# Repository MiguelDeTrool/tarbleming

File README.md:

# tarbleming
Arduino Nano based random looping sequencer Eurorack module

This is my take on the Music Thing Modular Turing Machine/Mutable Instruments Marbles, in an easier to implement fashion, with easily available through-hole parts. I must warn anyone attempting this that I have not tested these exact PCBs, only an earlier prototype, that I then made minor modifications to for this version. I am quite confident that they will work, and feel free to send me a message if you decide to try this out. I wouldn't recommend this to a complete beginner, as I have provided no build guide.

You'll also notice a manual is missing. Basic functionality to get up and running is send it a clock signal. Each sequence, wether Gate or CV, can have it's own length. Tap the corresponding button for however many steps you want, then do a quick double tap to confirm that value. Turn a sequence's Randomness knob fully clockwise for it to constantly change, and fully counter-clockwise for it to lock in a looping pattern. And again, if you have questions, feel free to send a message.

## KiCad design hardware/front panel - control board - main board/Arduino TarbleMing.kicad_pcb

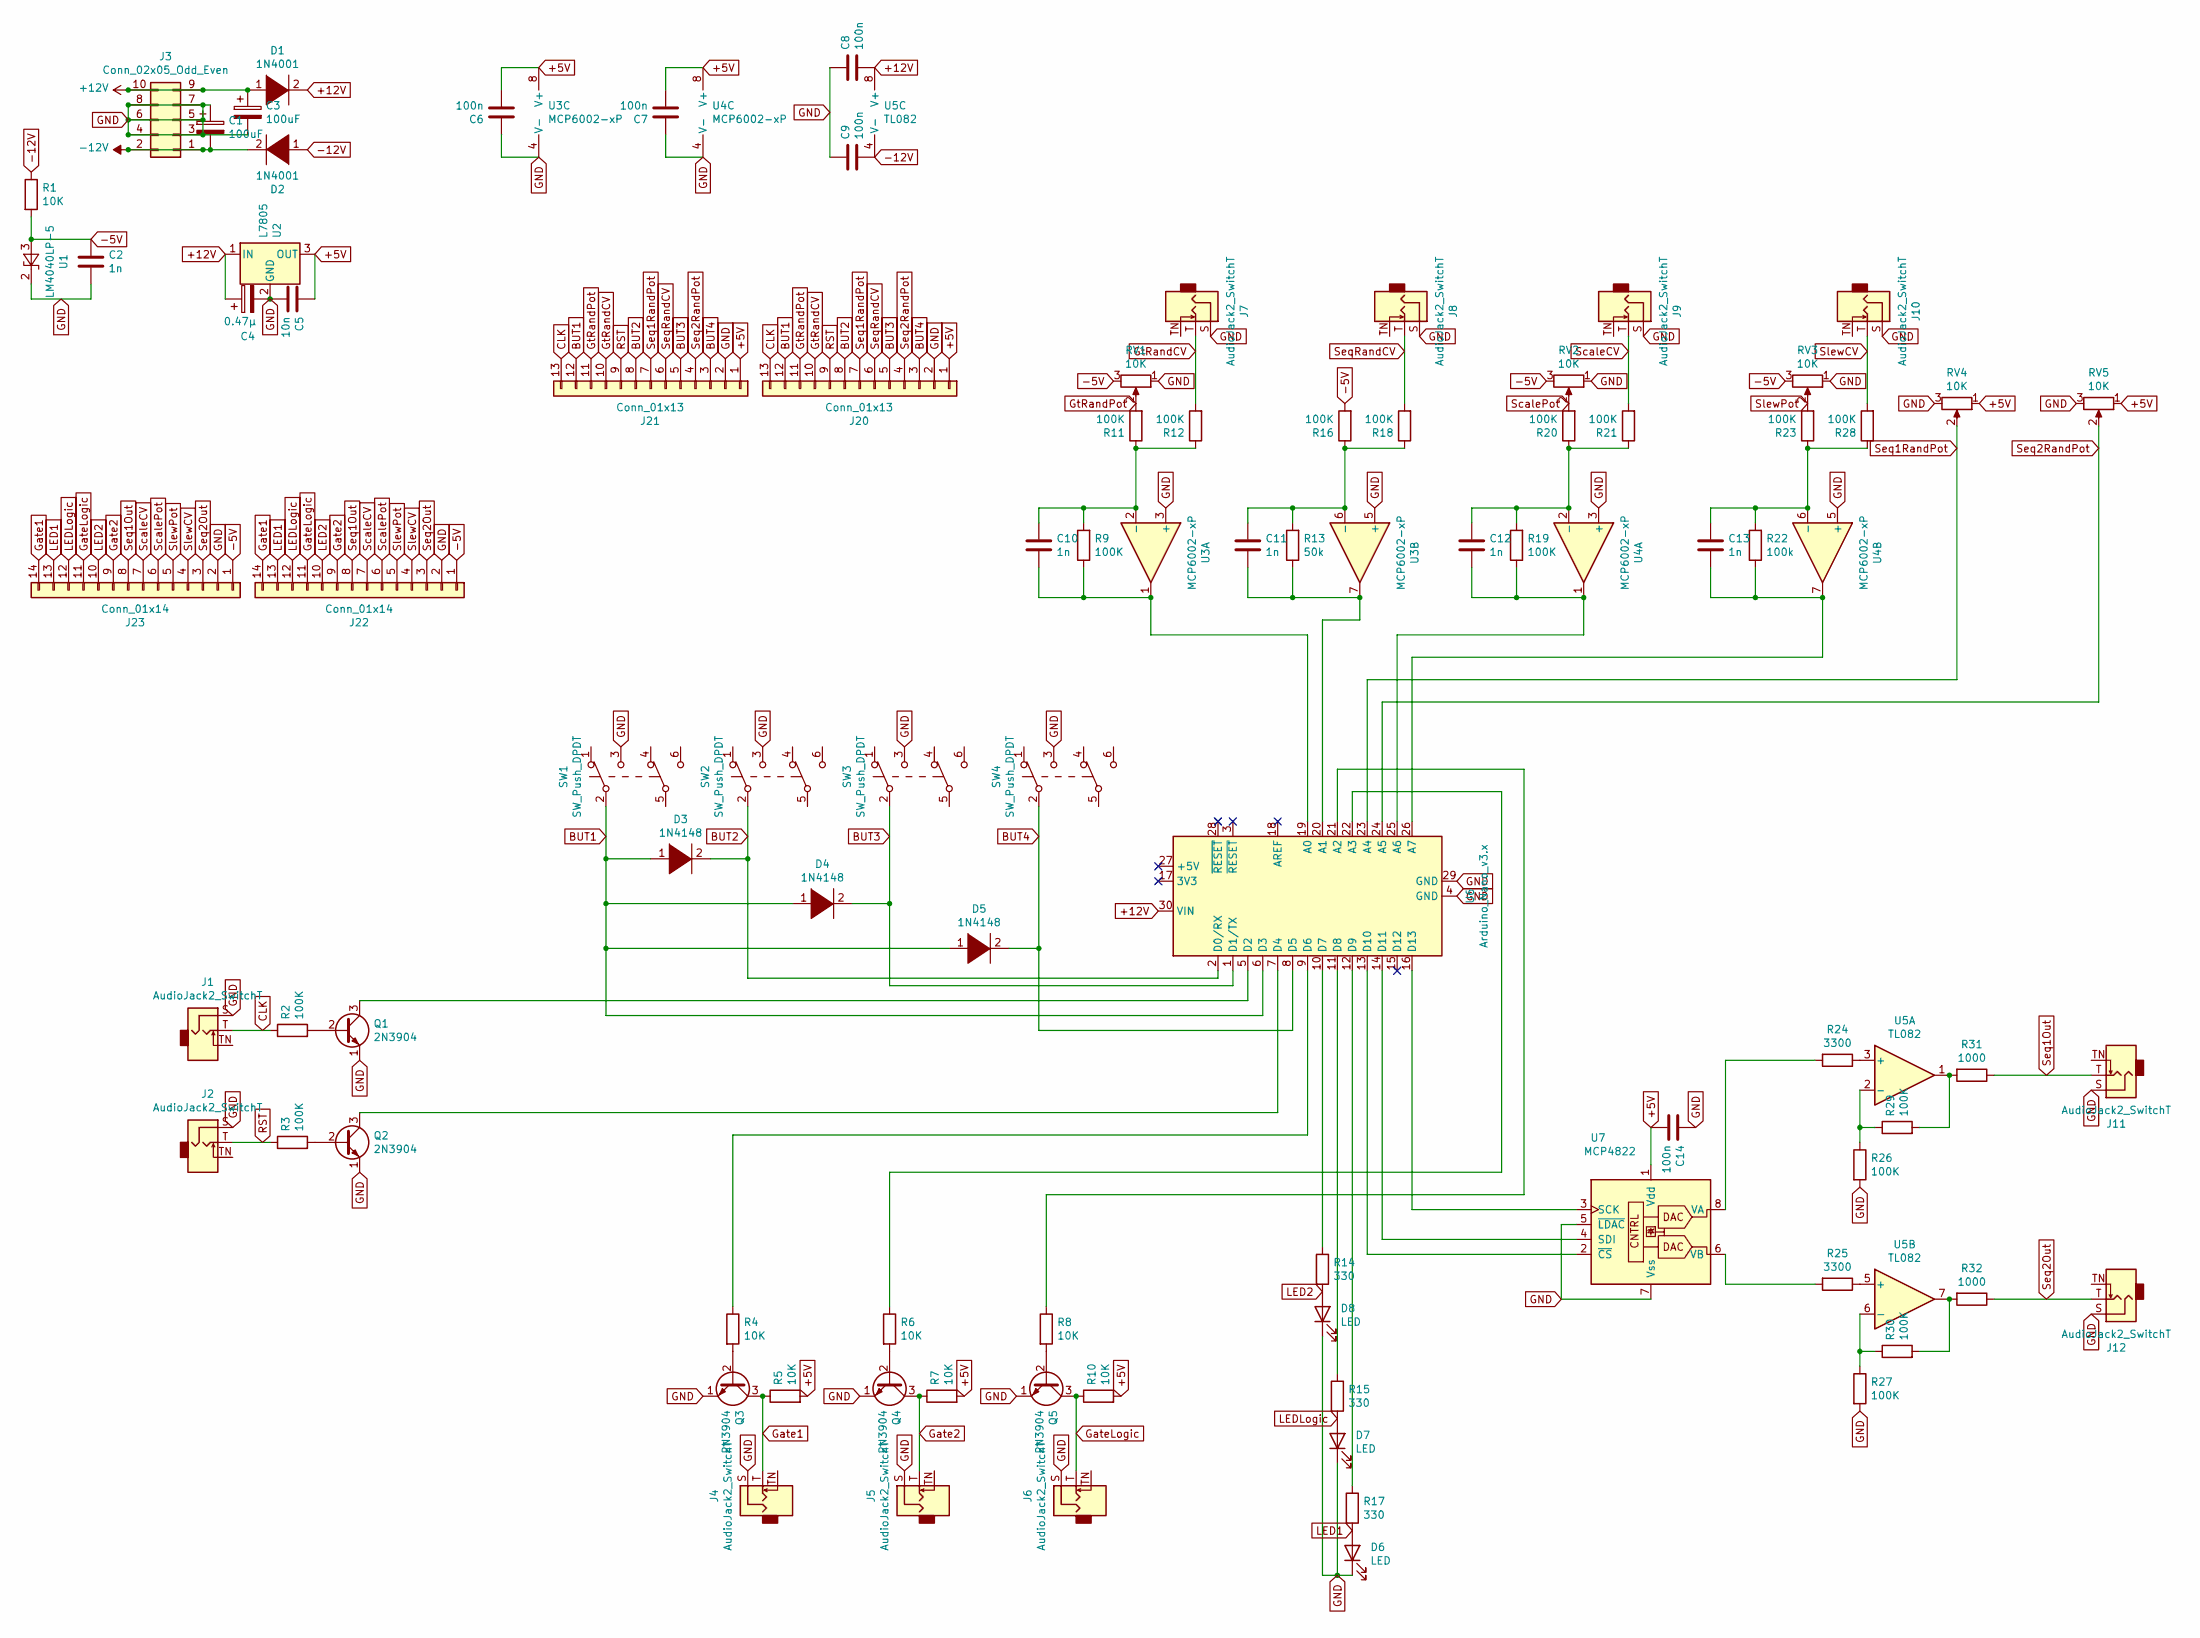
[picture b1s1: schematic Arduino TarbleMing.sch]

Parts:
C1, C3: 100uF; CP_Radial_D6.3mm_P2.50mm
C2, C10, C11, C12, C13: 1n; C_Disc_D3.8mm_W2.6mm_P2.50mm
C4: 0.47µ; C_Disc_D3.8mm_W2.6mm_P2.50mm
C5: 10n; C_Disc_D3.8mm_W2.6mm_P2.50mm
C6, C7, C8, C9, C14: 100n; C_Disc_D3.8mm_W2.6mm_P2.50mm
D1, D2: 1N4001; D_DO-15_P10.16mm_Horizontal
D3, D4, D5: 1N4148; D_DO-35_SOD27_P7.62mm_Horizontal
D6, D7, D8: LED; LED_D3.0mm
J1, J2, J4, J5, J6, J7, J8, J9, J10, J11, J12: AudioJack2_SwitchT; ModdedThonkiconn
J3: Conn_02x05_Odd_Even; PinHeader_2x05_P2.54mm_Vertical
J20, J21: Conn_01x13; PinHeader_1x13_P2.54mm_Vertical
J22, J23: Conn_01x14; PinHeader_1x14_P2.54mm_Vertical
Q1, Q2, Q3, Q4, Q5: 2N3904; TO-92_Inline
R1, R4, R5, R6, R7, R8, R10: 10K; R_Axial_DIN0207_L6.3mm_D2.5mm_P7.62mm_Horizontal
R2, R3, R9, R11, R12, R16, R18, R19, R20, R21, R23, R26, R27, R28, R29, R30: 100K; R_Axial_DIN0207_L6.3mm_D2.5mm_P7.62mm_Horizontal
R13: 50k; R_Axial_DIN0207_L6.3mm_D2.5mm_P7.62mm_Horizontal
R14, R15, R17: 330; R_Axial_DIN0207_L6.3mm_D2.5mm_P7.62mm_Horizontal
R22: 100k; R_Axial_DIN0207_L6.3mm_D2.5mm_P7.62mm_Horizontal
R24, R25: 3300; R_Axial_DIN0207_L6.3mm_D2.5mm_P7.62mm_Horizontal
R31, R32: 1000; R_Axial_DIN0207_L6.3mm_D2.5mm_P7.62mm_Horizontal
RV1, RV2, RV3, RV4, RV5: 10K; ModdedPotentiometer
SW1, SW2, SW3, SW4: SW_Push_DPDT; DPDT_Momentary_Push_Button_Switch
U1: LM4040LP-5; TO-92_Inline
U2: L7805; TO-220-3_Horizontal_TabDown
U3, U4: MCP6002-xP; DIP-8_W7.62mm_Socket_LongPads
U5: TL082; DIP-8_W7.62mm_Socket_LongPads
U6: Arduino_Nano_v3.x; Arduino_Nano
U7: MCP4822; DIP-8_W7.62mm_Socket_LongPads

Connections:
+5V: C5.1, C6.2, C7.2, C14.2, J20.1, J21.1, R5.2, R7.2, R10.2, RV4.1, RV5.1, U2.3 (OUT), U3.8 (V+), U4.8 (V+), U7.1 (Vdd)
+12V: C3.1, C4.1, C8.2, D1.1 (K), D1.2 (A), J3.9, J3.10, U2.1 (IN), U5.8 (V+), U6.30 (VIN)
-5V: C2.1, J22.1, J23.1, R1.2, R16.2, RV1.3, RV2.3, RV3.3, U1.3 (A)
-12V: C1.2, C9.2, D2.1 (K), D2.2 (A), J3.1, J3.2, R1.1, U5.4 (V-)
BUT1: D3.1 (K), D4.1 (K), D5.1 (K), J20.12, J21.12, SW1.2 (B), U6.6 (D3)
BUT2: D3.2 (A), J20.8, J21.8, SW2.2 (B), U6.2 (D0/RX)
BUT3: D4.2 (A), J20.5, J21.5, SW3.2 (B), U6.1 (D1/TX)
BUT4: D5.2 (A), J20.3, J21.3, SW4.2 (B), U6.8 (D5)
CLK: J1.T, J20.13, J21.13, R2.1
GND: C1.1, C2.2, C3.2, C4.2, C5.2, C6.1, C7.1, C8.1, C9.1, C14.1, D6.1 (K), D7.1 (K), D8.1 (K), J1.S, J2.S, J3.3, J3.4, J3.5, J3.6, J3.7, J3.8, J4.S, J5.S, J6.S, J7.S, J8.S, J9.S, J10.S, J11.S, J12.S, J20.2, J21.2, J22.2, J23.2, Q1.1 (E), Q2.1 (E), Q3.1 (E), Q4.1 (E), Q5.1 (E), R26.2, R27.2, RV1.1, RV2.1, RV3.1, RV4.3, RV5.3, SW1.3 (C), SW2.3 (C), SW3.3 (C), SW4.3 (C), U1.2 (K), U2.2 (GND), U3.3 (+), U3.4 (V-), U3.5 (+), U4.3 (+), U4.4 (V-), U4.5 (+), U6.4 (GND), U6.29 (GND), U7.5 (~LDAC), U7.7 (Vss)
Gate1: J4.T, J22.14, J23.14, Q3.3 (C), R5.1
Gate2: J5.T, J22.9, J23.9, Q4.3 (C), R7.1
GateLogic: J6.T, J22.11, J23.11, Q5.3 (C), R10.1
GtRandCV: J7.T, J20.10, J21.10, R12.2
GtRandPot: J20.11, J21.11, R11.2, RV1.2
LED1: D6.2 (A), J22.13, J23.13, R17.2
LED2: D8.2 (A), J22.10, J23.10, R14.2
LEDLogic: D7.2 (A), J22.12, J23.12, R15.2
unnamed: C10.1, R9.2, R11.1, R12.1, U3.2 (-)
unnamed: C10.2, R9.1, U3.1, U6.19 (A0)
unnamed: C11.1, R13.2, R16.1, R18.1, U3.6 (-)
unnamed: C11.2, R13.1, U3.7, U6.20 (A1)
unnamed: C12.1, R19.2, R20.1, R21.1, U4.2 (-)
unnamed: C12.2, R19.1, U4.1, U6.25 (A6)
unnamed: C13.1, R22.2, R23.1, R28.1, U4.6 (-)
unnamed: C13.2, R22.1, U4.7, U6.26 (A7)
unnamed: Q1.2 (B), R2.2
unnamed: Q1.3 (C), U6.5 (D2)
unnamed: Q2.2 (B), R3.2
unnamed: Q2.3 (C), U6.7 (D4)
unnamed: Q3.2 (B), R4.2
unnamed: Q4.2 (B), R6.2
unnamed: Q5.2 (B), R8.2
unnamed: R4.1, U6.9 (D6)
unnamed: R6.1, U6.22 (A3)
unnamed: R8.1, U6.21 (A2)
unnamed: R14.1, U6.10 (D7)
unnamed: R15.1, U6.11 (D8)
unnamed: R17.1, U6.12 (D9)
unnamed: R24.1, U5.3 (+)
unnamed: R24.2, U7.8 (VA)
unnamed: R25.1, U5.5 (+)
unnamed: R25.2, U7.6 (VB)
unnamed: R26.1, R29.1, U5.2 (-)
unnamed: R27.1, R30.1, U5.6 (-)
unnamed: R29.2, R31.2, U5.1
unnamed: R30.2, R32.2, U5.7
unnamed: U6.13 (D10), U7.2 (~CS)
unnamed: U6.14 (D11), U7.4 (SDI)
unnamed: U6.16 (D13), U7.3 (SCK)
RST: J2.T, J20.9, J21.9, R3.1
ScaleCV: J9.T, J22.7, J23.7, R21.2
ScalePot: J22.6, J23.6, R20.2, RV2.2
Seq1Out: J11.T, J22.8, J23.8, R31.1
Seq1RandPot: J20.7, J21.7, RV4.2, U6.23 (A4)
Seq2Out: J12.T, J22.3, J23.3, R32.1
Seq2RandPot: J20.4, J21.4, RV5.2, U6.24 (A5)
SeqRandCV: J8.T, J20.6, J21.6, R18.2
SlewCV: J10.T, J22.4, J23.4, R28.2
SlewPot: J22.5, J23.5, R23.2, RV3.2

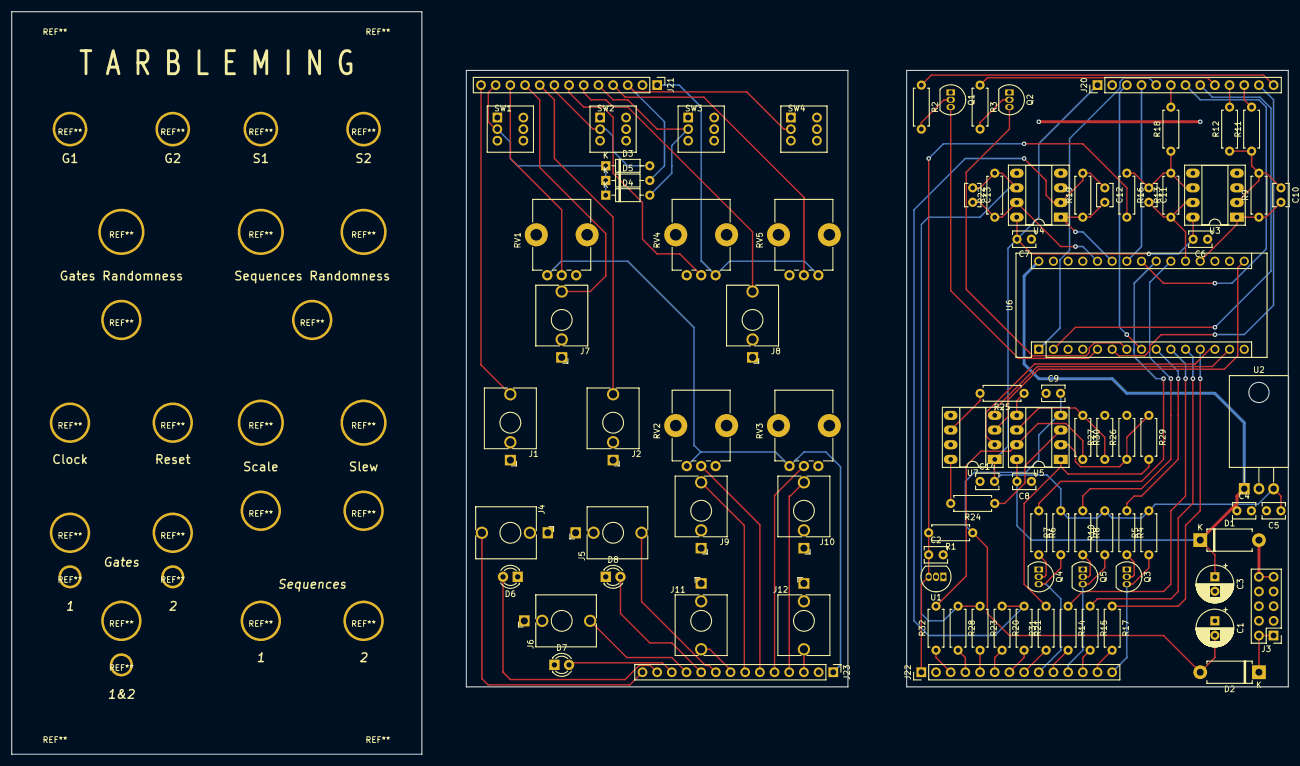
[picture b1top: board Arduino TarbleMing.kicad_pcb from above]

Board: 2 copper layers, 220.9 x 128.5 mm, 91 parts (0 on the bottom side), 60 nets.

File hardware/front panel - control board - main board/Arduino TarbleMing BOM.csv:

Id	Designator	Package	Quantity	Designation
1	R4,R5,R6,R10,R8,R7,R1	R_Axial_DIN0207_L6.3mm_D2.5mm_P7.62mm_Horizontal	7	10K
2	C14,C9,C8,C7,C6	C_Disc_D3.8mm_W2.6mm_P2.50mm	5	100n
3	R32,R31	R_Axial_DIN0207_L6.3mm_D2.5mm_P7.62mm_Horizontal	2	1000
4	Q4,Q5,Q3,Q2,Q1	TO-92_Inline	5	2N3904
5	U5	DIP-8_W7.62mm_Socket_LongPads	1	TL082
6	U7	DIP-8_W7.62mm_Socket_LongPads	1	MCP4822
7	U4,U3	DIP-8_W7.62mm_Socket_LongPads	2	MCP6002-xP
8	J23,J22	PinHeader_1x14_P2.54mm_Vertical	2	Conn_01x14
9	J21,J20	PinHeader_1x13_P2.54mm_Vertical	2	Conn_01x13
10	R23,R30,R29,R27,R26,R28,R21,R20,R19,R18,R16,R12,R11,R9,R3,R2,R22	R_Axial_DIN0207_L6.3mm_D2.5mm_P7.62mm_Horizontal	17	100K
11	D2,D1	D_DO-15_P10.16mm_Horizontal	2	1N4001
12	SW4,SW3,SW2,SW1	DPDT_Momentary_Push_Button_Switch	4	SW_Push_DPDT
13	D5,D4,D3	D_DO-35_SOD27_P7.62mm_Horizontal	3	1N4148
14	J12,J11,J10,J9,J8,J7,J6,J5,J4,J2,J1	ModdedThonkiconn	11	ThonkiConn
15	U6	Arduino_Nano	1	Arduino_Nano_v3.x
16	U2	TO-220-3_Horizontal_TabDown	1	L7805
17	U1	TO-92_Inline	1	LM4040LP-5
18	RV5,RV4,RV3,RV2,RV1	ModdedPotentiometer	5	10K
19	R25,R24	R_Axial_DIN0207_L6.3mm_D2.5mm_P7.62mm_Horizontal	2	3300
20	R14,R15,R17	R_Axial_DIN0207_L6.3mm_D2.5mm_P7.62mm_Horizontal	3	330
21	R13	R_Axial_DIN0207_L6.3mm_D2.5mm_P7.62mm_Horizontal	1	50k
22	J3	PinHeader_2x05_P2.54mm_Vertical	1	Eurorack Power Header
23	D8,D7,D6	LED_D3.0mm	3	LED
24	C3,C1	CP_Radial_D6.3mm_P2.50mm	2	100uF
25	C13,C12,C11,C10,C2	C_Disc_D3.8mm_W2.6mm_P2.50mm	5	1n
26	C5	C_Disc_D3.8mm_W2.6mm_P2.50mm	1	10n
27	C4	C_Disc_D3.8mm_W2.6mm_P2.50mm	1	0.47µ

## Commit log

2021-04-21 Create LICENSE
